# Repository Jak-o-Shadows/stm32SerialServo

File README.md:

# stm32SerialServo
A PCB and code for a STM32 servo controller - small.

A tiny (fits on the back of a 9 gram servo fairly neatly) 4 channel servo driver. Serial, with future expansion to CAN. Uses a STM32F042F6P6 for high resolution servo driving.

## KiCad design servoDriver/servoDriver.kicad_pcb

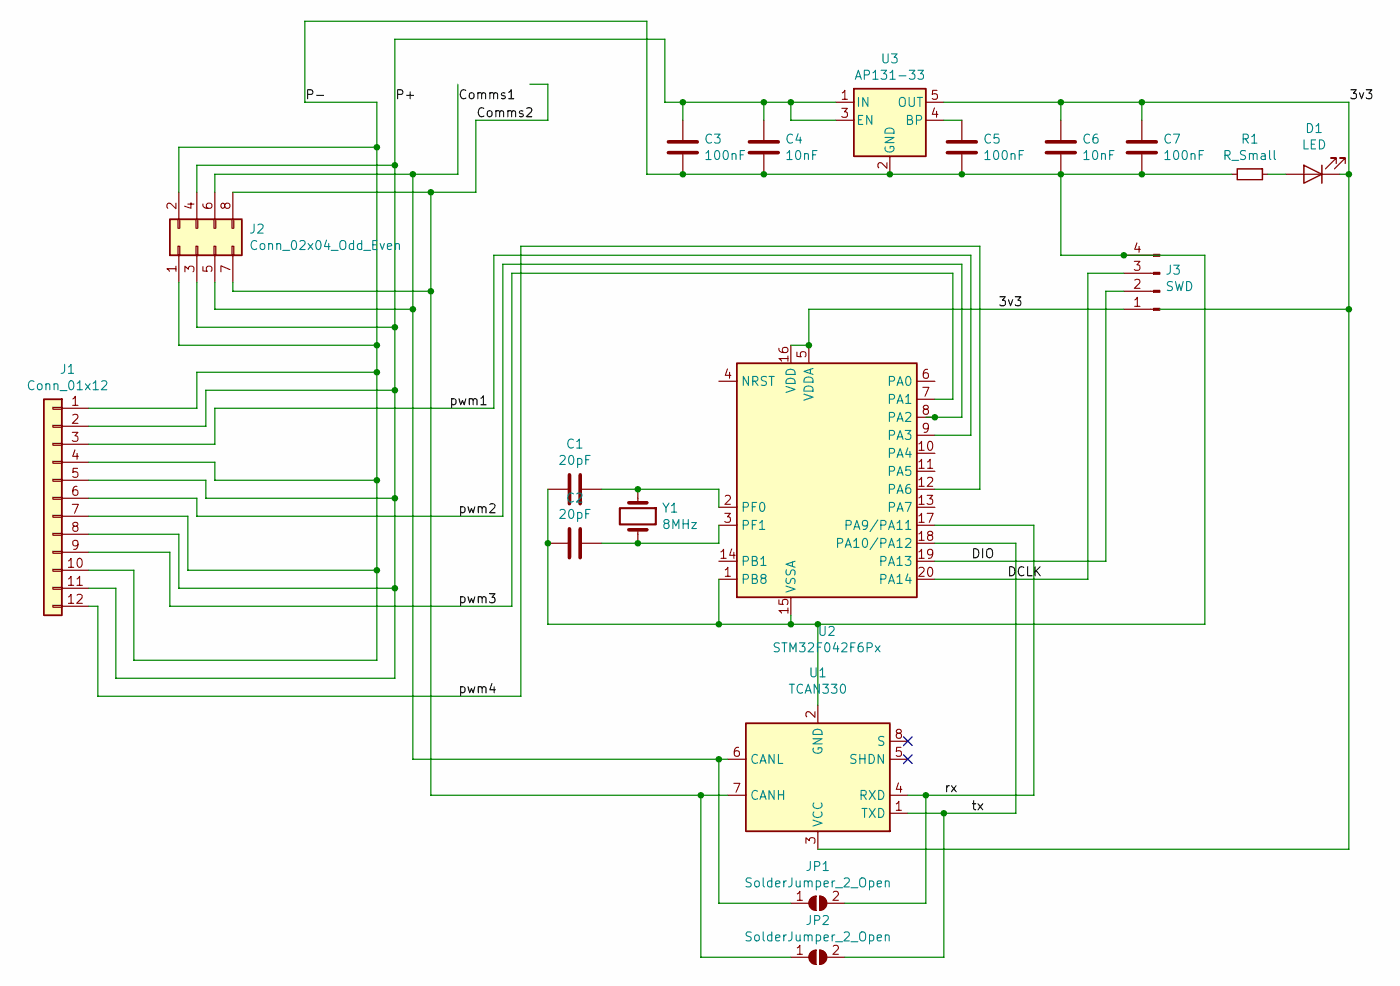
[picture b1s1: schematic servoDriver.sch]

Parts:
C1, C2: 20pF; C_0805_2012Metric_Pad1.15x1.40mm_HandSolder
C3, C5, C7: 100nF; C_0805_2012Metric_Pad1.15x1.40mm_HandSolder
C4, C6: 10nF; C_0805_2012Metric_Pad1.15x1.40mm_HandSolder
D1: LED; LED_0603_1608Metric
J1: Conn_01x12; PinHeader_3x04_P2.54mm_Vertical
J2: Conn_02x04_Odd_Even
J3: SWD; PinHeader_1x04_P1.27mm_Vertical
JP1, JP2: SolderJumper_2_Open; SolderJumper-2_P1.3mm_Open_RoundedPad1.0x1.5mm
R1: R_Small; R_0603_1608Metric
U1: TCAN330; SOT-23-8_Handsoldering
U2: STM32F042F6Px; TSSOP-20_4.4x6.5mm_P0.65mm
U3: AP131-33; SOT-23-5
Y1: 8MHz; Crystal_SMD_5032-2Pin_5.0x3.2mm_HandSoldering

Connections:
/3v3: C6.2, C7.2, D1.1 (K), J3.1, U1.3 (VCC), U2.5 (VDDA), U2.16 (VDD), U3.5 (OUT)
/Comms1: J2.5, J2.6, JP1.1 (A), U1.6 (CANL)
/Comms2: J2.7, J2.8, JP2.1 (A), U1.7 (CANH)
/DCLK: J3.3, U2.20 (PA14)
/DIO: J3.2, U2.19 (PA13)
/P+: C3.2, C4.2, J1.2, J1.5, J1.8, J1.11, J2.3, J2.4, U3.1 (IN), U3.3 (EN)
/P-: C1.2, C2.2, C3.1, C4.1, C5.1, C6.1, C7.1, J1.1, J1.4, J1.7, J1.10, J2.1, J2.2, J3.4, R1.2, U1.2 (GND), U2.1 (PB8), U2.15 (VSSA), U3.2 (GND)
/pwm1: J1.3, U2.9 (PA3)
/pwm2: J1.6, U2.8 (PA2)
/pwm3: J1.9, U2.7 (PA1)
/pwm4: J1.12, U2.12 (PA6)
/rx: JP1.2 (B), U1.4 (RXD), U2.17 (PA9/PA11)
/tx: JP2.2 (B), U1.1 (TXD), U2.18 (PA10/PA12)
unnamed: C1.1, U2.2 (PF0), Y1.1
unnamed: C2.1, U2.3 (PF1), Y1.2
unnamed: C5.2, U3.4 (BP)
unnamed: D1.2 (A), R1.1

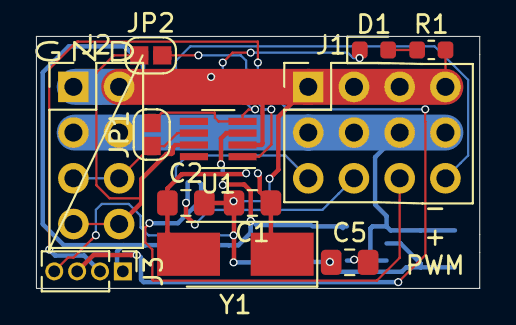
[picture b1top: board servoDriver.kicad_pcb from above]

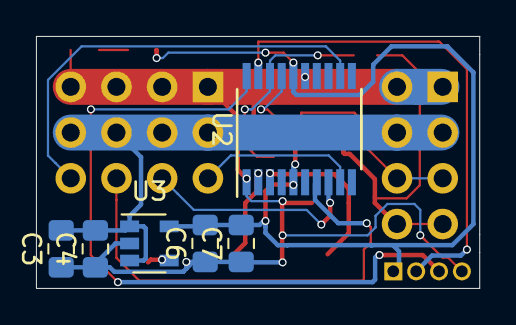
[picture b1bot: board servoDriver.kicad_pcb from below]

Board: 2 copper layers, 24.6 x 14.0 mm, 18 parts (6 on the bottom side), 17 nets.

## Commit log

2020-04-19 Docs from STM
2020-04-19 PCB Design 1
2020-04-19 Manufactured PCB design 1
2020-07-26 Basic board working! Very small bodges (Boot1/Pin 1 needs to be ground), but it pretty much just worked.
2020-08-08 Implement serial protocol from https://github.com/Jak-o-Shadows/StubbyHexapodStm32
2020-08-14 Move the serial servo communications stuff to separate include files.
2020-10-21 Version 2 PCB?
2020-10-23 Working! Updating PWM value in a sequence from another timer.
2020-11-13 Multiple channels independently going through point sequences.
2020-12-12 PCB updates * V3 * Added extra channel * Using closely spaced pins.
2020-12-12 Different lights sequence.
2020-12-20 Version 3
2020-12-20 V2, V3 zips
2021-02-14 Switch to working in degrees, rather than magical assorted number of clock tips.
2021-02-14 Use 0 as a special value to turn the servos off.
2021-09-11 Add 4th servo channel for v3 PCB
2021-09-11 added playback of a sequence for xmas lights.
2021-09-12 Tidyup, make sequences auto-restart, and set initial on/off of a Command * The latter allows for polarity control - ie for h-bridges.
2021-09-27 Sequence suitable for an 8 strand (4x up and over doubles) christmas tree
